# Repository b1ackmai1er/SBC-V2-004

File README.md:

# SBC-V2-004
 Retrobrew Computers SBC-V2 development

 Updated design to include the following changes.

    Correction of reset circuit.
    Addition of speaker circuit.
    Add solder jumpers for bypassing DS1210.
    Move status LED to corner of board as per other ECB boards.
    Align serial connector pinout and functionality to SBC Z180 Mark IV
    Add max232 solder jumpers for TTL level output.
    Add onboard super capacitor.
    Incorporate ppide.
    Update to Kicad 5.
    Add jumper settings to silkscreen.
    Move reset switch to edge of board and remove reset jumper.
    Add jumpers to configure battery backup source.
    Add cpu clock divider to support MSX.
    Default to hard Kontron reset mode.

Other ideas to be considered:

    RAM access over ECB-BUS.
    Renumber all parts.

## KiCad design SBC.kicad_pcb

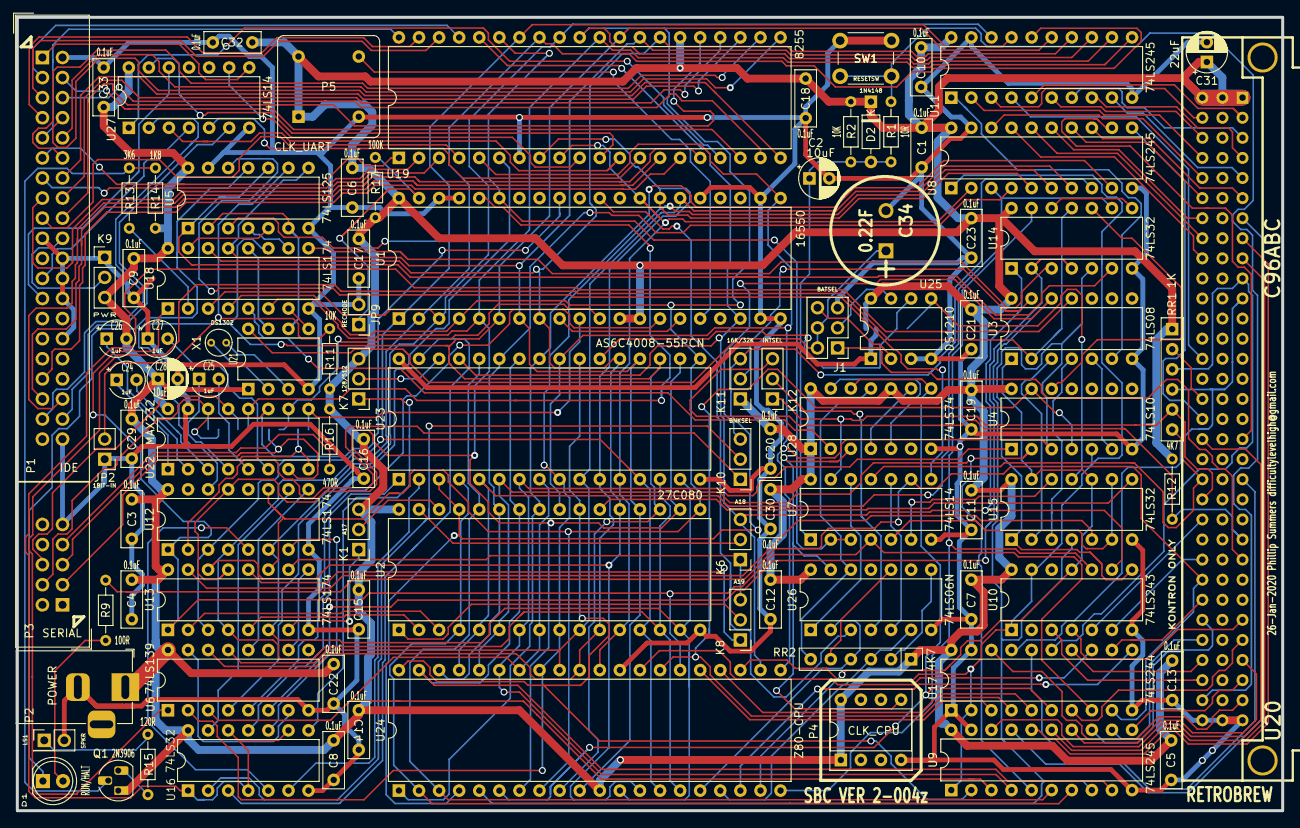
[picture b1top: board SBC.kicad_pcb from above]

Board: 2 copper layers, 160.0 x 100.3 mm, 102 parts (0 on the bottom side), 203 nets.

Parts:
C1, C3, C4, C5, C6, C7, C8, C9, C10, C11, C12, C13, C14, C15, C16, C17, C18, C19, C20, C21, C22, C23, C29, C30, C32, C33: 0.1uF; C_Disc_D7.0mm_W2.5mm_P5.00mm
C2, C28: 10uF; CP_Radial_D5.0mm_P2.50mm
C24, C25, C26, C27: 1uF; CP_Radial_Tantal_D4.5mm_P2.50mm
C31: 22uF; CP_Radial_D5.0mm_P2.50mm
C34: 0.22F; SuperCap5
D1: RUN/HALT; LED_D5.0mm
D2: 1N4148; D_DO-35_SOD27_P7.62mm_Horizontal
J1: BATSEL; PinHeader_2x03_P2.54mm_Vertical
JP2: 1BIT-IN; PinHeader_1x02_P2.54mm_Vertical
JP3: RAMVCC; SolderJumper-2_P1.3mm_Open_RoundedPad1.0x1.5mm
JP4: RAMCS; SolderJumper-2_P1.3mm_Open_RoundedPad1.0x1.5mm
JP5: RXD; SolderJumper-2_P1.3mm_Open_RoundedPad1.0x1.5mm
JP6: CTS; SolderJumper-2_P1.3mm_Open_RoundedPad1.0x1.5mm
JP7: TXD; SolderJumper-2_P1.3mm_Open_RoundedPad1.0x1.5mm
JP8: RTS; SolderJumper-2_P1.3mm_Open_RoundedPad1.0x1.5mm
JP9: RECMODE; PinHeader_1x02_P2.54mm_Vertical
K1: A17; PinHeader_1x03_P2.54mm_Vertical
K6: A18; PinHeader_1x03_P2.54mm_Vertical
K7: 128/512; PinHeader_1x03_P2.54mm_Vertical
K8: A19; PinHeader_1x03_P2.54mm_Vertical
K9: PWR; PinHeader_1x03_P2.54mm_Vertical
K10: BNKSEL; PinHeader_1x03_P2.54mm_Vertical
K11: 16K/32K; PinHeader_1x03_P2.54mm_Vertical
K12: INTSEL; PinHeader_1x03_P2.54mm_Vertical
LS1: SPKR; PinHeader_2x01_P2.54mm_Vertical
P1: IDE; IDC-Header_2x20_P2.54mm_Vertical
P2: POWER; BarrelJack_Horizontal
P3: SERIAL; IDC-Header_2x05_P2.54mm_Vertical
P4: CLK_CPU; DIP-8_W7.62mm_Socket
P5: CLK_UART; Oscillator_DIP-8
Q1: 2N3906; TO-92_HandSolder
R1: 10R; R_Axial_DIN0204_L3.6mm_D1.6mm_P7.62mm_Horizontal
R2, R11: 10K; R_Axial_DIN0204_L3.6mm_D1.6mm_P7.62mm_Horizontal
R9: 100R; R_Axial_DIN0204_L3.6mm_D1.6mm_P7.62mm_Horizontal
R12: 4K7; R_Axial_DIN0204_L3.6mm_D1.6mm_P7.62mm_Horizontal
R13: 3K6; R_Axial_DIN0204_L3.6mm_D1.6mm_P7.62mm_Horizontal
R14: 1K8; R_Axial_DIN0204_L3.6mm_D1.6mm_P7.62mm_Horizontal
R15: 120R; R_Axial_DIN0204_L3.6mm_D1.6mm_P7.62mm_Horizontal
R16: 470R; R_Axial_DIN0204_L3.6mm_D1.6mm_P7.62mm_Horizontal
R17: 100K; R_Axial_DIN0204_L3.6mm_D1.6mm_P7.62mm_Horizontal
RR1: 1K; R_Array_SIP6
RR2: 4K7; R_Array_SIP6
SW1: RESETSW; SW_PUSH_6mm_H8mm
U1: 16550; DIP-40_W15.24mm
U2: 27C080; DIP-32_W15.24mm
U3: 74LS08; DIP-14_W7.62mm
U4: 74LS10; DIP-14_W7.62mm
U5: 74LS125; DIP-14_W7.62mm
U6: 74LS139; DIP-16_W7.62mm
U7, U27: 74LS14; DIP-14_W7.62mm
U8, U9, U11: 74LS245; DIP-20_W7.62mm
U10: 74LS243; DIP-14_W7.62mm
U12, U13, U18: 74LS174; DIP-16_W7.62mm
U14, U15, U16: 74LS32; DIP-14_W7.62mm
U17: 74LS244; DIP-20_W7.62mm
U19: 8255; DIP-40_W15.24mm
U20: C96ABC; C96ABCMC
U21: DS1302; DIP-8_W7.62mm
U22: MAX232; DIP-16_W7.62mm
U23: AS6C4008-55PCN; DIP-32_W15.24mm
U24: Z80-CPU; DIP-40_W15.24mm
U25: DS1210; DIP-8_W7.62mm
U26: 74LS06N; DIP-14_W7.62mm
U28: 74LS74; DIP-14_W7.62mm
X1: CRYSTAL; Crystal_Round_D3.0mm_Vertical

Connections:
/-PC3: P1.37, U27.2
/-PC4: P1.38, U27.6
/-PC5: P1.23, U27.4
/-PC6: P1.25, U27.12
/-PC7: P1.1, U27.8
//BUSAK: U4.5, U8.1, U9.1, U10.1, U10.13, U17.2, U24.23
//BUSRQ: U17.3, U24.25
//CS_CFG: U6.7, U6.15
//CS_CFG1: U6.12, U12.9
//CS_CFG2: U6.10, U13.9
//CS_PPI: U6.4, U19.6
//CS_RAM: JP4.1, U15.11, U25.5
//CS_ROM: U2.22, U15.8
//CS_RTC: U6.6, U14.2, U14.4
//CS_UART: U1.14, U6.5
//HALT: U17.11, U24.18
//INT: RR2.4, U24.16, U26.2
//IORQ: U10.10, U14.13, U24.20
//IOSEL: U3.2, U6.1, U14.11
//M1: U4.4, U4.13, U17.4, U24.27
//MREQ: U3.1, U10.11, U15.10, U15.13, U24.19
//NMI: RR2.3, U24.17, U26.6
//RD: U1.21, U2.24, U4.3, U10.8, U14.5, U15.1, U19.5, U23.24, U24.21
//RESET: U7.4, U12.1, U13.1, U17.8, U18.1, U24.26
//RESET_IN: R1.2, SW1.2, U20.C31
//RFSH: U17.13, U24.28
//ROM_ENABLE: U13.15, U15.5
//RTC_RD: U5.1, U5.10, U14.6
//RTC_WR: U14.3, U18.9
//WAIT: U17.5, U24.24
//WR: K6.3, U1.18, U10.9, U14.1, U19.36, U23.29, U24.22
/A0: U1.28, U2.12, U8.2, U19.9, U23.12, U24.30
/A1: U1.27, U2.11, U6.14, U8.5, U19.8, U23.11, U24.31
/A2: U1.26, U2.10, U6.13, U8.7, U23.10, U24.32
/A3: U2.9, U6.2, U8.6, U23.9, U24.33
/A4: U2.8, U6.3, U9.3, U23.8, U24.34
/A5: U2.7, U4.1, U9.4, U23.7, U24.35
/A6: U2.6, U4.2, U9.5, U23.6, U24.36
/A7: U2.5, U8.3, U14.9, U23.5, U24.37
/A8: U2.27, U8.4, U23.27, U24.38
/A9: U2.26, U9.9, U23.26, U24.39
/A10: U2.23, U9.2, U23.23, U24.40
/A11: U2.25, U8.9, U23.25, U24.1
/A12: U2.4, U9.7, U23.4, U24.2
/A13: U2.28, U9.6, U23.28, U24.3
/A14: K11.3, U2.29, U8.8, U23.3, U24.4
/A15: K10.3, U3.12, U9.8, U15.4, U24.5
/A15_RAM: U16.3, U23.31
/A15_ROM: U2.3, U13.2
/A16_RAM: U16.6, U23.2
/A16_ROM: U2.2, U13.5
/A17_RAM: K7.1, U16.8
/A17_ROM: K1.1, U13.7
/A18_RAM: U16.11, U23.1
/A18_ROM: K6.1, K8.3, U13.10
/A19_ROM: K8.1, U13.12
/BUF_Q4: U18.7, U21.5
/BUF_Q5: U5.4, U18.10
/BUF_Q6: U18.12, U21.7
/BUF_Q7: U5.5, U18.15
/B_/BUSAK: U17.18, U20.A31
/B_/BUSRQ: RR1.4, U17.17, U20.A11
/B_/HALT: R9.2, U7.9, U17.9, U20.C25
/B_/IEO: RR1.2, U20.C16
/B_/INT: K12.1, RR1.5, U7.13, U20.C21
/B_/IORQ: U10.4, U20.A27
/B_/M1: U17.16, U20.A20
/B_/MREQ: U10.3, U20.C30
/B_/NMI: RR1.6, U7.11, U20.C20
/B_/RD: U10.6, U20.C24
/B_/RESOUT: U17.12, U20.C26
/B_/RFSH: U17.7, U20.A28
/B_/WAIT: RR1.3, U17.15, U20.A10
/B_/WR: U10.5, U20.C22
/B_A0: U8.18, U20.C5
/B_A1: U8.15, U20.C7
/B_A2: U8.13, U20.A6
/B_A3: U8.14, U20.C6
/B_A4: U9.17, U20.A7
/B_A5: U9.16, U20.A8
/B_A6: U9.15, U20.A9
/B_A7: U8.17, U20.C9
/B_A8: U8.16, U20.C8
/B_A9: U9.11, U20.A30
/B_A10: U9.18, U20.C18
/B_A11: U8.11, U20.C17
/B_A12: U9.13, U20.C27
/B_A13: U9.14, U20.A29
/B_A14: U8.12, U20.A18
/B_A15: U9.12, U20.C28
/B_BAT: J1.1, U20.A24
/B_CLK_CPU: U17.14, U20.C29
/B_D0: U11.3, U20.C2
/B_D1: U11.4, U20.C14
/B_D2: U11.2, U20.C4
/B_D3: U11.8, U20.A4
/B_D4: U11.9, U20.A5
/B_D5: U11.5, U20.A2
/B_D6: U11.7, U20.A3
/B_D7: U11.6, U20.C3
/CFG1_Q0: K10.1, U12.2
/CFG1_Q1: U12.5, U16.5
/CFG1_Q2: U12.7, U16.10
/CFG1_Q3: U12.10, U16.13
/CLKSEL: U18.5, U28.2
/CLK_CPU: U17.6, U24.6, U28.8, U28.12
/CLK_UART: P5.5, U1.16
/CTS: JP6.2, P3.6, U22.13
/CTS_TTL: JP6.1, U1.36, U22.12
/D0: U1.1, U2.13, U5.3, U11.17, U12.3, U13.3, U19.34, U23.13, U24.14
/D1: U1.2, U2.14, U11.16, U12.4, U13.4, U19.33, U23.14, U24.15
/D2: U1.3, U2.15, U11.18, U12.6, U13.6, U18.3, U19.32, U23.15, U24.12
/D3: U1.4, U2.17, U11.12, U12.11, U13.11, U18.4, U19.31, U23.17, U24.8
/D4: U1.5, U2.18, U11.11, U12.13, U13.13, U18.6, U19.30, U23.18, U24.7
/D5: U1.6, U2.19, U11.15, U12.14, U18.11, U19.29, U23.19, U24.9
/D6: U1.7, U2.20, U5.8, U11.13, U18.13, U19.28, U23.20, U24.10
/D7: U1.8, U2.21, U11.14, U13.14, U18.14, U19.27, U23.21, U24.13
/DATA_DIR: U3.6, U11.1
/DTR: P3.7, R16.2
/INT: U1.30, U26.3
/PA0: P1.17, U19.4
/PA1: P1.15, U19.3
/PA2: P1.13, U19.2
/PA3: P1.11, U19.1
/PA4: P1.9, U19.40
/PA5: P1.7, U19.39
/PA6: P1.5, U19.38
/PA7: P1.3, U19.37
/PB0: P1.4, U19.18
/PB1: P1.6, U19.19
/PB2: P1.8, U19.20
/PB3: P1.10, U19.21
/PB4: P1.12, U19.22
/PB5: P1.14, U19.23
/PB6: P1.16, U19.24
/PB7: P1.18, U19.25
/PC0: P1.35, U19.14
/PC1: P1.33, U19.15
/PC2: P1.36, U19.16
/PC3: U19.17, U27.1
/PC4: U19.13, U27.5
/PC5: U19.12, U27.3
/PC6: U19.11, U27.13
/PC7: U19.10, U27.9
/PU4K7-A: RR2.2, U26.8
/PU4K7-B: RR2.5, U26.10
/PU4K7-C: RR2.6, U26.12, U28.11
/RESET: U1.35, U7.2, U7.3, U19.35
/RTC_DQ: U5.2, U5.6, U21.6
/RTS: JP8.2, P3.4, U22.14
/RTS_TTL: JP8.1, U1.32, U22.11
/RX: JP5.2, P3.3, U22.8
/SIN_TTL: JP5.1, U1.10, U22.9
/SOUT_TTL: JP7.1, U1.11, U22.10
/TX: JP7.2, P3.5, U22.7
/VBAT1: J1.6, U25.2
/VBAT2: J1.3, U25.7
/VCC_SRAM: JP3.2, U23.32, U25.1
/~B_IQ0: K12.3, R12.2, U20.A23
GND: C1.2, C2.2, C3.2, C4.2, C5.2, C6.2, C7.2, C8.2, C9.2, C10.2, C11.2, C12.2, C13.2, C14.2, C15.2, C16.2, C17.2, C18.2, C19.2, C20.2, C21.2, C22.2, C23.2, C27.1, C28.2, C29.2, C30.2, C31.2, C32.2, C33.2, C34.2, J1.5, JP2.1, JP9.2, K9.1, LS1.2, P1.2, P1.19, P1.22, P1.24, P1.26, P1.30, P1.40, P2.2, P3.9, P4.4, P5.4, SW1.1, U1.19, U1.20, U1.22, U1.25, U1.37, U1.38, U2.16, U3.7, U4.7, U5.7, U5.13, U6.8, U7.7, U8.10, U8.19, U9.10, U9.19, U10.7, U11.10, U11.19, U12.8, U13.8, U14.7, U15.7, U16.7, U17.1, U17.10, U17.19, U18.8, U19.7, U20.A32, U20.B32, U20.C32, U21.4, U22.15, U23.16, U24.29, U25.3, U25.4, U26.7, U27.7, U28.7
unnamed: C2.1, D2.2, R1.1, R2.2, U7.1
unnamed: C24.1, U22.1
unnamed: C24.2, U22.3
unnamed: C25.1, U22.4
unnamed: C25.2, U22.5
unnamed: C26.1, U22.2
unnamed: C27.2, U22.6
unnamed: C34.1, J1.2, J1.4, U21.8
unnamed: D1.1, U5.11
unnamed: D1.2, R9.1
unnamed: JP2.2, R11.2, U5.9
unnamed: JP4.2, U23.22, U25.6
unnamed: JP9.1, R17.1, U1.39
unnamed: K1.2, U2.30
unnamed: K6.2, U2.31
unnamed: K7.2, U23.30
unnamed: K8.2, U2.1
unnamed: K9.2, P1.20
unnamed: K10.2, U16.2
unnamed: K11.2, U3.13
unnamed: K12.2, U26.4
unnamed: LS1.1, R15.1
unnamed: P4.5, U26.13, U28.3
unnamed: Q1.2, R13.1, R14.1
unnamed: Q1.3, R15.2
unnamed: R13.2, U18.2
unnamed: U1.9, U1.15
unnamed: U3.5, U4.6
unnamed: U5.12, U7.8
unnamed: U4.12, U14.10
unnamed: U14.8, U14.12
unnamed: U3.3, U15.2
unnamed: U3.4, U15.3
unnamed: U7.5, U15.6, U15.9
unnamed: U7.6, U15.12
unnamed: U3.11, U16.1, U16.4, U16.9, U16.12
unnamed: U21.2, X1.2
unnamed: U21.3, X1.1
unnamed: U7.12, U26.1
unnamed: U7.10, U26.5
unnamed: U28.4, U28.9
unnamed: U28.5, U28.13
VCC: C1.1, C3.1, C4.1, C5.1, C6.1, C7.1, C8.1, C9.1, C10.1, C11.1, C12.1, C13.1, C14.1, C15.1, C16.1, C17.1, C18.1, C19.1, C20.1, C21.1, C22.1, C23.1, C26.2, C28.1, C29.1, C30.1, C31.1, C32.1, C33.1, D2.1, JP3.1, K1.3, K7.3, K9.3, K11.1, P2.1, P4.1, P4.8, P5.1, P5.8, Q1.1, R2.1, R11.1, R12.1, R14.2, R16.1, R17.2, RR1.1, RR2.1, U1.12, U1.13, U1.40, U2.32, U3.14, U4.14, U5.14, U6.16, U7.14, U8.20, U9.20, U10.14, U11.20, U12.16, U13.16, U14.14, U15.14, U16.14, U17.20, U18.16, U19.26, U20.A1, U20.B1, U20.C1, U21.1, U22.16, U24.11, U25.8, U26.14, U27.14, U28.1, U28.10, U28.14

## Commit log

2019-09-24 Version B
2019-09-24 Version C
2019-09-24 Version D
2019-09-24 Version E
2019-09-24 Version F
2019-09-24 Version G
2019-09-24 Version H
2019-09-24 Version I
2019-09-24 Version J
2019-09-24 Version K
2019-09-24 Version L
2019-09-24 Version M
2019-09-24 Version N
2019-09-24 Version O
2019-09-24 Version P
2019-09-24 Version Q
2019-09-24 Version R
2019-09-24 Version S
2019-09-24 Version T
2019-09-24 Version U
2019-09-24 Version V
2019-09-24 Version W
2019-09-24 Version X
2020-01-28 Version Y
2020-01-28 Version Z
